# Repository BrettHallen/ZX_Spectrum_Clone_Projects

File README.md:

# ZX Spectrum Clone Projects
Hardware projects & information for Sinclair ZX Spectrum clone computers

## [Datasheets](/Datasheets)
Relevant datasheets for PCB designs.<br>

## [Astra](/Astra)
Information about the Soviet Spectrum clone.<br>

## [Belarus Byte DIN to VGA](/Belarus_Byte_DIN-to-VGA)
Convert 5-pin DIN video output to DE15 VGA:

- Pin 1 = synch
- Pin 2 = ground
- Pin 3 = blue
- Pin 4 = green
- Pin 5 = red

## [ESP32 Rainbow Nunchuck Interface](/ESP32_Rainbow_Nunchuck_Interface)
A small QWIIC-to-Nunchuck interface adaptor board for the [ESP32 Rainbow](https://www.esp32rainbow.com).

## [Leningrad-2 DIN to VGA](/Leningrad_2_DIN-to-VGA)
Convert 5-pin DIN video output to DE15 VGA:

- Pin 1 = audio
- Pin 2 = blue
- Pin 3 = red
- Pin 4 = video
- Pin 5 = green
- Sheath = ground

## [Leningrad 2 Expansion](/Leningrad_2_Expansion)
Experimental board to convert the 2x32 (2.5mm pin pitch) expansion header to standard ZX Spectrum edge connector.

## [Moldova BYTE DIN to VGA](/Moldova_BYTE_DIN-to-VGA)
There are two types of BYTE from Moldova: the "Red BYTE" (in a red case with 7-pin DIN) and the "Speccy BYTE" (looks like a Spectrum with a 5-pin DIN).

- Pin 1 = composite video (not connected)
- Pin 2 = composite synch
- Pin 3 = blue
- Pin 4 = green
- Pin 5 = red
- Pin 6 = ground
- Pin 7 = audio

## [Nafanya](/Nafanya)

## [Orel BK DIN to VGA](/Orel_BK_DIN-to-VGA)

## [RGB to VGA](/RGB_to_VGA)

## [Sirius](/Sirius)

## [ZX Spectrum Pioneer 2 Keyboard](/ZX_Spectrum_Pioneer-2_Keyboard)
Work in progress replacement.

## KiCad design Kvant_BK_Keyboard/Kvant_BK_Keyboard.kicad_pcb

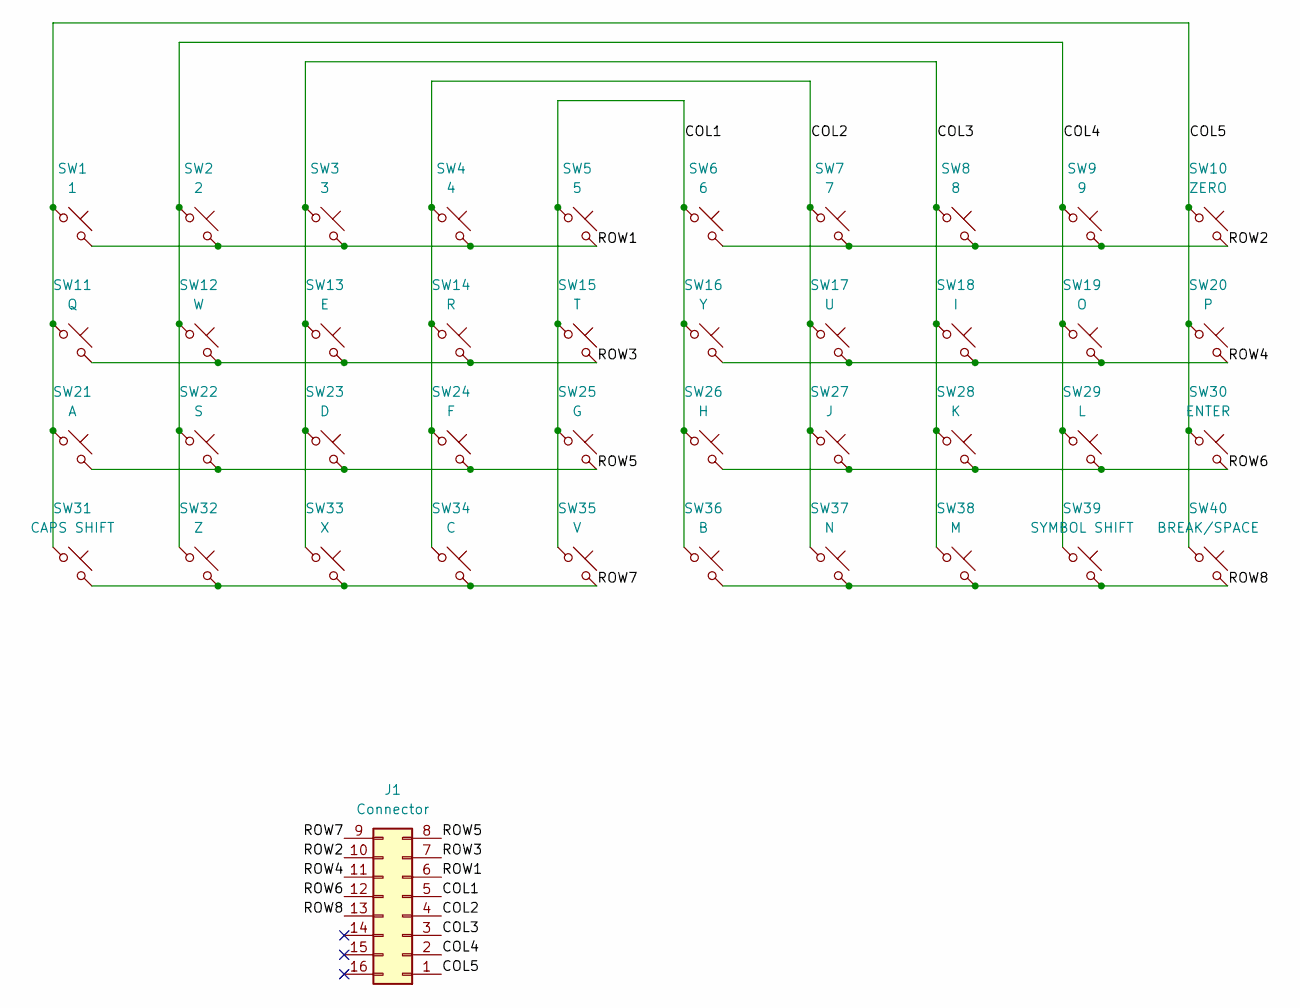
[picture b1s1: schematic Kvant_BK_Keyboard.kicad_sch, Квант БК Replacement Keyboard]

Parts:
J1: Connector; DIP-16_W7.62mm
SW1: 1; SW_KS33_1u
SW2: 2; SW_KS33_1u
SW3: 3; SW_KS33_1u
SW4: 4; SW_KS33_1u
SW5: 5; SW_KS33_1u
SW6: 6; SW_KS33_1u
SW7: 7; SW_KS33_1u
SW8: 8; SW_KS33_1u
SW9: 9; SW_KS33_1u
SW10: ZERO; SW_KS33_1u
SW11: Q; SW_KS33_1u
SW12: W; SW_KS33_1u
SW13: E; SW_KS33_1u
SW14: R; SW_KS33_1u
SW15: T; SW_KS33_1u
SW16: Y; SW_KS33_1u
SW17: U; SW_KS33_1u
SW18: I; SW_KS33_1u
SW19: O; SW_KS33_1u
SW20: P; SW_KS33_1u
SW21: A; SW_KS33_1u
SW22: S; SW_KS33_1u
SW23: D; SW_KS33_1u
SW24: F; SW_KS33_1u
SW25: G; SW_KS33_1u
SW26: H; SW_KS33_1u
SW27: J; SW_KS33_1u
SW28: K; SW_KS33_1u
SW29: L; SW_KS33_1u
SW30: ENTER; SW_KS33_1u
SW31: CAPS SHIFT; SW_KS33_1u
SW32: Z; SW_KS33_1u
SW33: X; SW_KS33_1u
SW34: C; SW_KS33_1u
SW35: V; SW_KS33_1u
SW36: B; SW_KS33_1u
SW37: N; SW_KS33_1u
SW38: M; SW_KS33_1u
SW39: SYMBOL SHIFT; SW_KS33_1u
SW40: BREAK/SPACE; SW_KS33_1u

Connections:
/COL1: J1.5, SW5.1, SW6.1, SW15.1, SW16.1, SW25.1, SW26.1, SW35.1, SW36.1
/COL2: J1.4, SW4.1, SW7.1, SW14.1, SW17.1, SW24.1, SW27.1, SW34.1, SW37.1
/COL3: J1.3, SW3.1, SW8.1, SW13.1, SW18.1, SW23.1, SW28.1, SW33.1, SW38.1
/COL4: J1.2, SW2.1, SW9.1, SW12.1, SW19.1, SW22.1, SW29.1, SW32.1, SW39.1
/COL5: J1.1, SW1.1, SW10.1, SW11.1, SW20.1, SW21.1, SW30.1, SW31.1, SW40.1
/ROW1: J1.6, SW1.2, SW2.2, SW3.2, SW4.2, SW5.2
/ROW2: J1.10, SW6.2, SW7.2, SW8.2, SW9.2, SW10.2
/ROW3: J1.7, SW11.2, SW12.2, SW13.2, SW14.2, SW15.2
/ROW4: J1.11, SW16.2, SW17.2, SW18.2, SW19.2, SW20.2
/ROW5: J1.8, SW21.2, SW22.2, SW23.2, SW24.2, SW25.2
/ROW6: J1.12, SW26.2, SW27.2, SW28.2, SW29.2, SW30.2
/ROW7: J1.9, SW31.2, SW32.2, SW33.2, SW34.2, SW35.2
/ROW8: J1.13, SW36.2, SW37.2, SW38.2, SW39.2, SW40.2

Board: 2 copper layers, 41 parts (1 on the bottom side), 13 nets, no tracks yet.

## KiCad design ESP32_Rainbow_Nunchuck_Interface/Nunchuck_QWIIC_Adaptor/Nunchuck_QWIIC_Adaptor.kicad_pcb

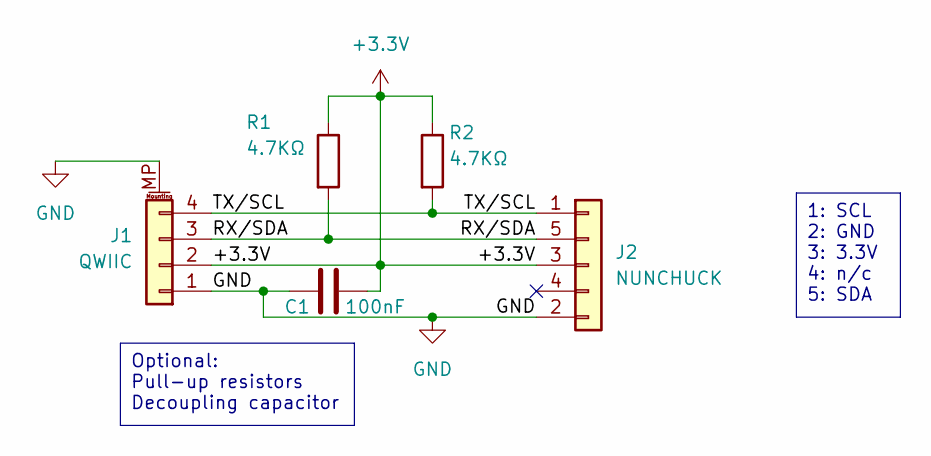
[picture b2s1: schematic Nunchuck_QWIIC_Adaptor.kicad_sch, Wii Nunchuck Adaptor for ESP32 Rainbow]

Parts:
C1: 100nF; C_0805_2012Metric_Pad1.18x1.45mm_HandSolder
J1: QWIIC; JST_SH_SM04B-SRSS-TB_1x04-1MP_P1.00mm_Horizontal
J2: NUNCHUCK; Wii_Nunchuck_Edge_Connector
R1, R2: 4.7KΩ; R_0805_2012Metric_Pad1.20x1.40mm_HandSolder

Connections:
+3.3V: C1.1, J1.2, J2.3, R1.1, R2.1
/RX/SDA: J1.3, J2.5, R1.2
/TX/SCL: J1.4, J2.1, R2.2
GND: C1.2, J1.1, J1.MP (MountPin), J2.2

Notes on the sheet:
Optional: Pull-up resistors Decoupling capacitor
1: SCL 2: GND 3: 3.3V 4: n/c 5: SDA

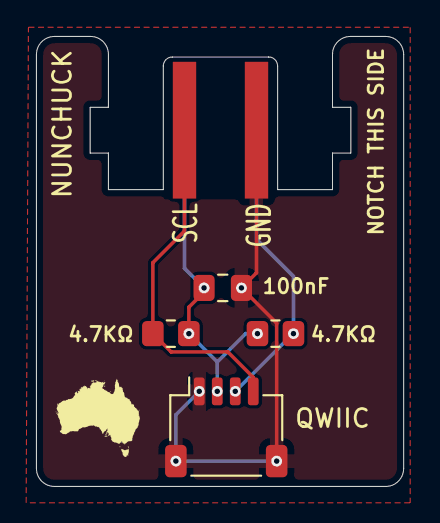
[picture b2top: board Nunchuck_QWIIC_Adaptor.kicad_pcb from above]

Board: 2 copper layers, 20.4 x 25.0 mm, 5 parts (0 on the bottom side), 4 nets.

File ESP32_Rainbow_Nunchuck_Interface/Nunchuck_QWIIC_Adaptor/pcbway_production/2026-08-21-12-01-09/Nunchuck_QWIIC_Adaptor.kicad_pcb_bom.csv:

Designator,Quantity,Value,Footprint,Package,MPN,DNP,Mount_Type,Description,KiLib_Generator
C1,1,100nF,C_0805_2012Metric_Pad1.18x1.45mm_HandSolder,,,,smt,Unpolarized capacitor,SMD_2terminal_chip_molded
J1,1,QWIIC,JST_SH_SM04B-SRSS-TB_1x04-1MP_P1.00mm_Horizontal,,,,smt,"Generic connectable mounting pin connector, single row, 01x04, script generated (kicad-library-utils/schlib/autogen/connector/)",connector/SMD_single_row_plus_mounting_pad
J2,1,NUNCHUCK,Wii_Nunchuck_Edge_Connector,,,,smt,"Generic connector, single row, 01x05, script generated (kicad-library-utils/schlib/autogen/connector/)",
"R1, R2",2,4.7KΩ,R_0805_2012Metric_Pad1.20x1.40mm_HandSolder,,,,smt,Resistor,SMD_2terminal_chip_molded

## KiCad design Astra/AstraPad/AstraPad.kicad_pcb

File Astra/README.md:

# Astra/Астра Information
A Soviet-era Sinclair ZX Spectrum clone from Minsk in the Byelorussian SSR.<br>

Its full name is "Универсальная Телеигровая Приставка Астра", or "Universal Television Game Console Astra".<br>

The files found here are from [ZXBYTE's site](https://zxbyte.org), translated to English where required and with my own additional information added.<br>

## [АСТРАПАД](/Astra/AstraPad)
My attempt at a simple Joypad-style design for the Astra.<br>

## [ROMs](/Astra/ROMs)
The Astra has two 8KB ROMs containing the modified Spectrum firmware: the changes are the [boot screen](/Astra/Images/Astra_Boot_Screen.png) and the [character font](/Astra/Images/Astra_vs_ZX_font.png) (reminds me of the Amstrad CPC font).

It also has four small PROMs - one is socketed.  I plan to (try to) dump the other three using these [Arduino sketches](/Astra/Arduino_PROM_dumper).

## [Schematics](/Astra/Schematics)
Schematics and board layout with Western-equivalent part IDs added.<br>

IMPORTANT - several of the interface pinouts have conflicting pin assignments when comparing the schematic with the manual.  The manual pinout matches my machine.<br>

## Cassette Pinout (X1)
The cassette interface uses a 5-pin DIN labelled "МАГ" (Магнетофон).<br>

IMPORTANT NOTE!  The [schematic pinout](/Astra/Schematics/X1_Pinout_RU.jpg) disagrees with the [manual pinout](/Astra/Schematics/Astra_Manual_Pinout.jpeg)!  For my machine I have used the manual's pinout.<br>

Note that the schematic lists IN FL (signal 33) and OUT FL (signal 34) but I can't see where they are used.<br>

| Pin | Signal         |
|-----|----------------|
| 1   | EAR (Вх. Маг)  |
| 2   | Ground (0V)    |
| 3   | MIC (Вых. Маг) |
| 4   | IN FL (?)      |
| 5   | OUT FL (?)     |

Now if we look at the manual's pinout:<br>

| Pin | Signal      |
|-----|-------------|
| 1   | MIC (Выход) |
| 2   | Ground (0V) |
| 3   | EAR (Вход)  |
| 4   |             |
| 5   |             |

## Video Pinout (X3)
The audio and video are output via a 2x4 РГ1Н-1 connector labelled "ТВ".  On the [schematic](/Astra/Schematics/X3_Pinout_RU.jpg) it is interface "X3".<br>

| Pin | Signal                   |
|-----|--------------------------|
| 1   | Brightness (8/16)        |
| 2   | Blue                     |
| 3   | Green                    |
| 4   | Red                      |
| 5   | Video (Видео)            |
| 6   | Audio (УНЧ)              |
| 7   | Inverted sync (Инверсия) |
| 8   | Ground (Общий)           |

The manual pinout lists pin 1 as "Полутон" or half-tone which seems to match.<br>

## Power Pinout (X4)
The power input is a 5-pin DIN labelled "БП" (Блок Питания).  On the schematic is it interface "X4", but in the [manual pinout](/Astra/Schematics/Astra_Manual_Pinout.jpeg) it is interface "X2".<br>

Note that the schematic lists ±12V but I don't see it actually used - signals 31 & 32 on the schematic - follow the manual pinout.<br>

| Pin | Signal   |
|-----|----------|
| 1   | +5V      |
| 2   |          |
| 3   | 0V       |
| 4   | -12V (?) |
| 5   | +12V (?) |

## Useful Links
- [ZXBYTE](https://zxbyte.org/astra.htm)

## Youtube Videos
- [Part 1: First look](https://youtu.be/gDP2ERXGaYo)
- [Part 2: Power on - NOK](https://youtu.be/xESQuC1y398)
- [Part 3: It works!](https://youtu.be/SmFEAmI-PiA)
- [Part 4: Loading a game](https://youtu.be/jdW-dMJSBxg)
- [Part 5: Bodging together a joypad](https://youtu.be/Pdt0EjIXJ0o)

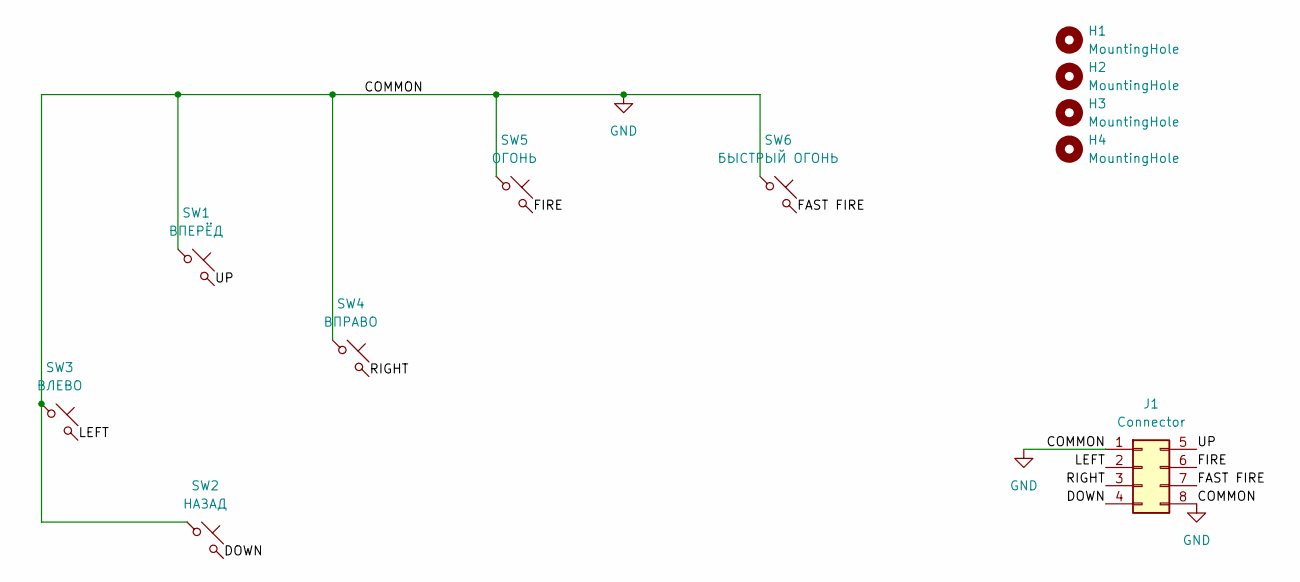
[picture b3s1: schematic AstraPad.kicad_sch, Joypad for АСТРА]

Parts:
H1, H2, H3, H4: MountingHole; MountingHole_3.2mm_M3_DIN965
J1: Connector; PinHeader_2x04_P2.54mm_Vertical
SW1: ВПЕРЁД; SW_PUSH-12mm
SW2: НАЗАД; SW_PUSH-12mm
SW3: ВЛЕВО; SW_PUSH-12mm
SW4: ВПРАВО; SW_PUSH-12mm
SW5: ОГОНЬ; SW_PUSH-12mm
SW6: БЫСТРЫЙ ОГОНЬ; SW_PUSH-12mm

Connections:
/DOWN: J1.4, SW2.2
/FAST FIRE: J1.7, SW6.2
/FIRE: J1.6, SW5.2
/LEFT: J1.2, SW3.2
/RIGHT: J1.3, SW4.2
/UP: J1.5, SW1.2
GND: J1.1, J1.8, SW1.1, SW2.1, SW3.1, SW4.1, SW5.1, SW6.1

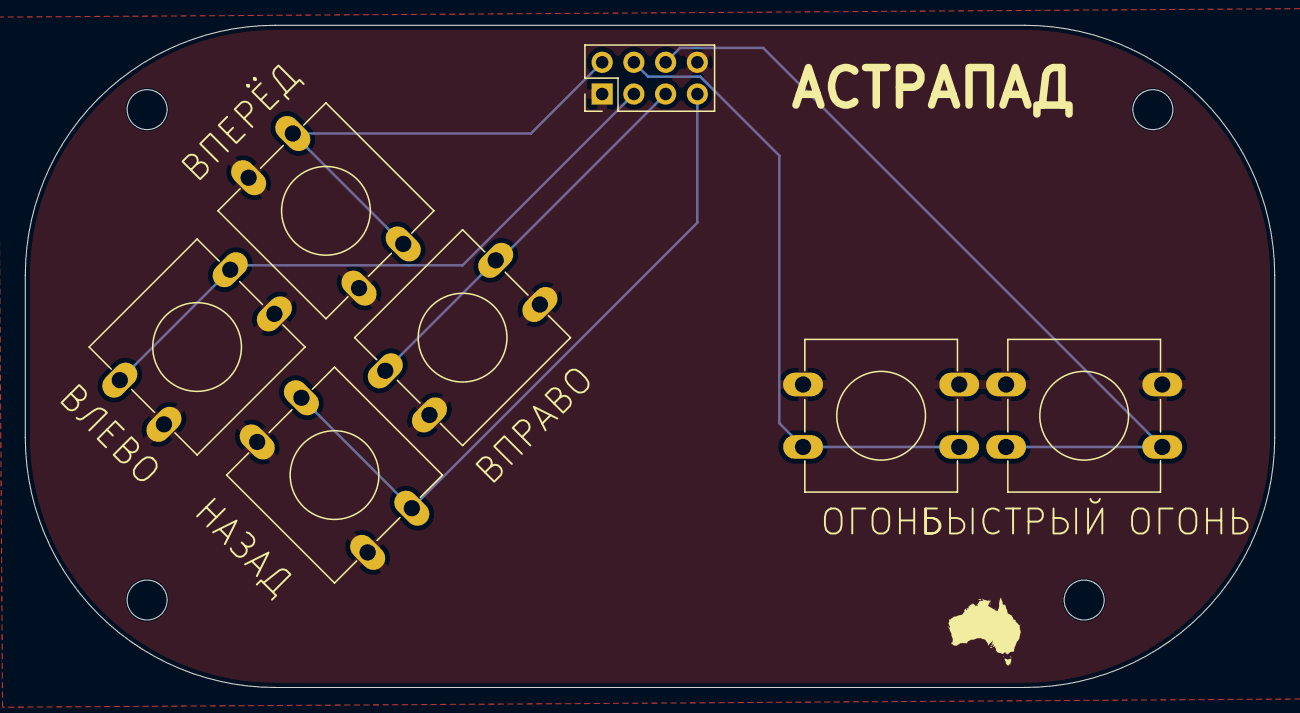
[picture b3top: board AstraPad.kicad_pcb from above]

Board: 2 copper layers, 100.0 x 53.0 mm, 11 parts (0 on the bottom side), 7 nets.

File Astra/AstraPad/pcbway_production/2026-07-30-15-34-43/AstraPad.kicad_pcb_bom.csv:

Designator,Quantity,Value,Footprint,Package,MPN,DNP,Mount_Type,Description,KiLib_Generator
J1,1,Connector,PinHeader_2x04_P2.54mm_Vertical,,,,tht,"Generic connector, double row, 02x04, top/bottom pin numbering scheme (row 1: 1...pins_per_row, row2: pins_per_row+1 ... num_pins), script generated (kicad-library-utils/schlib/autogen/connector/)",connector/pin_header_socket
SW1,1,ВПЕРЁД,SW_PUSH-12mm,,,,tht,"Push button switch, normally open, two pins, 45° tilted",
SW2,1,НАЗАД,SW_PUSH-12mm,,,,tht,"Push button switch, normally open, two pins, 45° tilted",
SW3,1,ВЛЕВО,SW_PUSH-12mm,,,,tht,"Push button switch, normally open, two pins, 45° tilted",
SW4,1,ВПРАВО,SW_PUSH-12mm,,,,tht,"Push button switch, normally open, two pins, 45° tilted",
SW5,1,ОГОНЬ,SW_PUSH-12mm,,,,tht,"Push button switch, normally open, two pins, 45° tilted",
SW6,1,БЫСТРЫЙ ОГОНЬ,SW_PUSH-12mm,,,,tht,"Push button switch, normally open, two pins, 45° tilted",

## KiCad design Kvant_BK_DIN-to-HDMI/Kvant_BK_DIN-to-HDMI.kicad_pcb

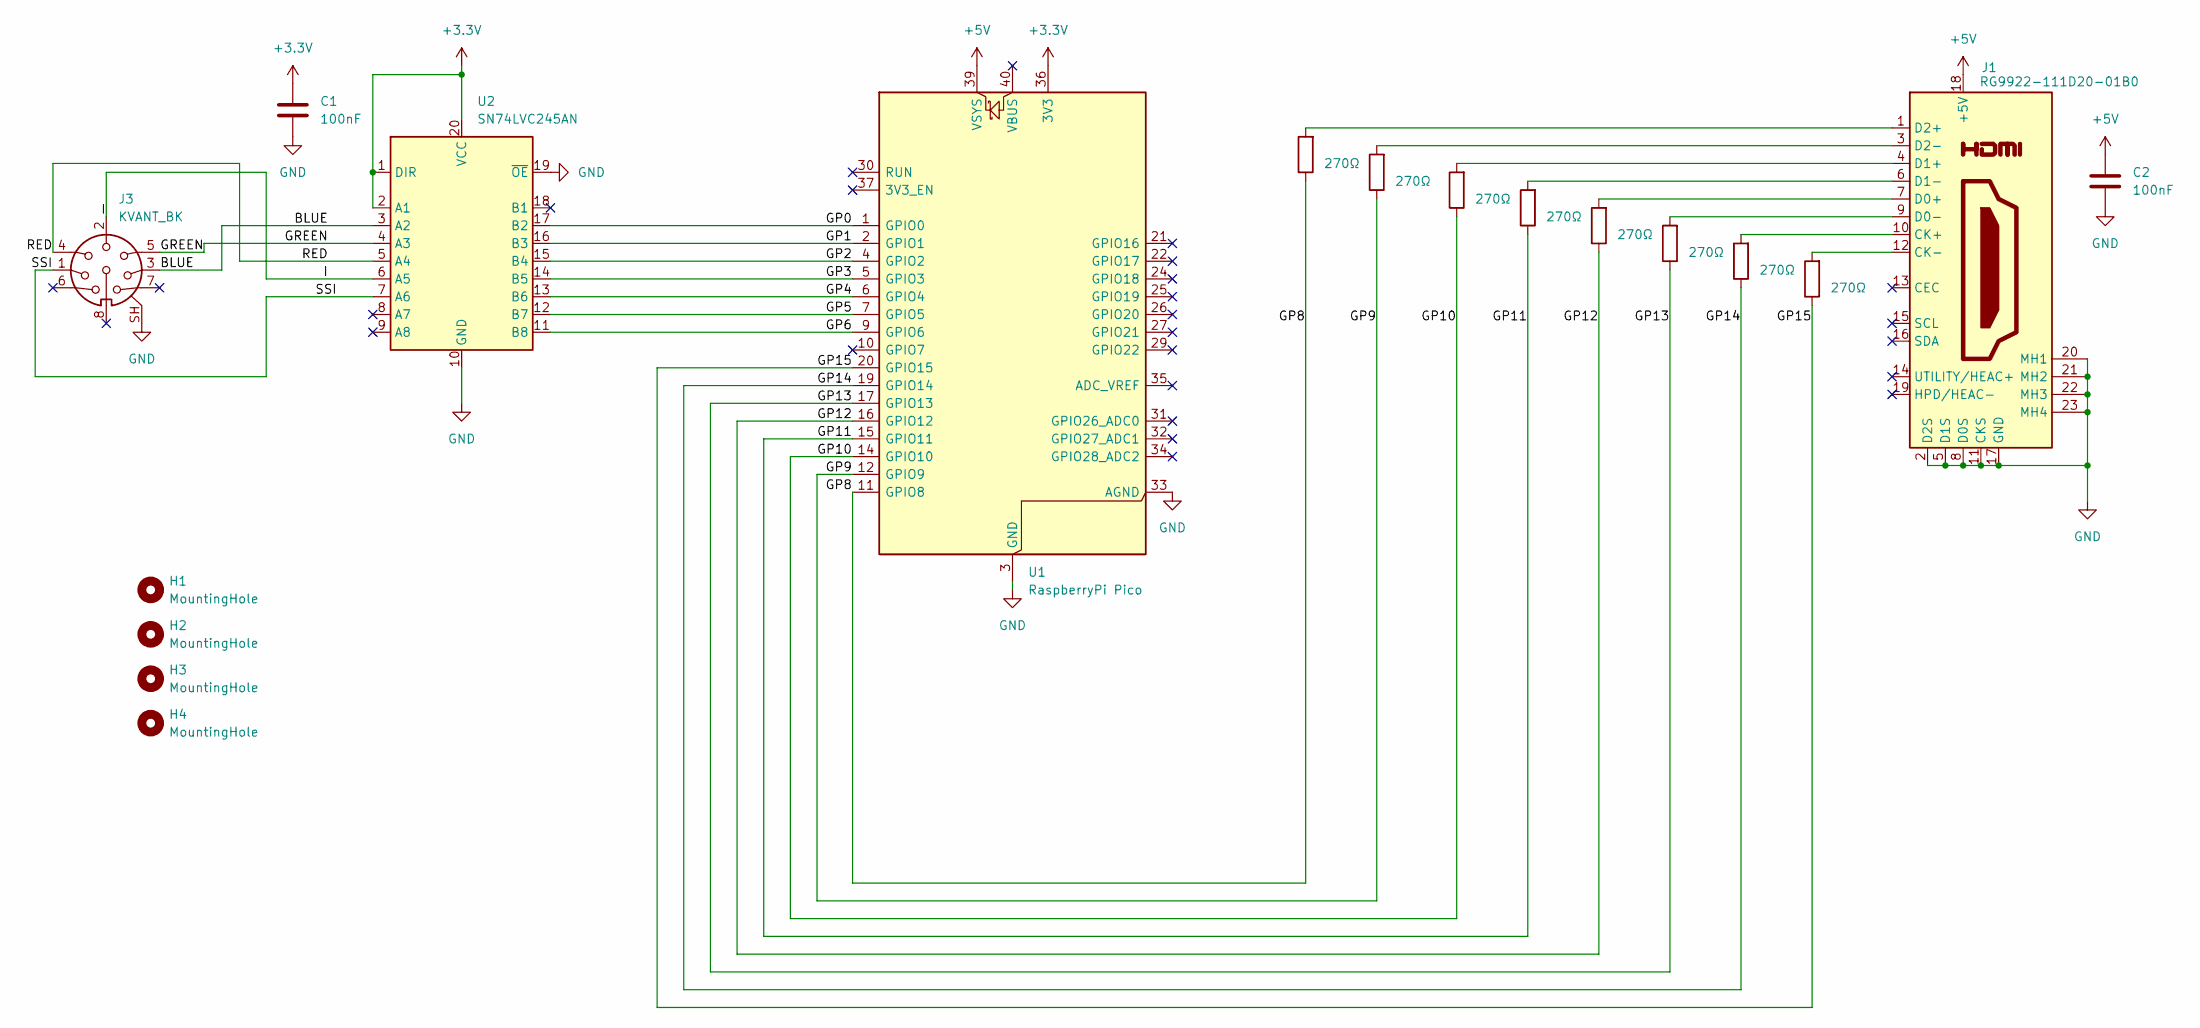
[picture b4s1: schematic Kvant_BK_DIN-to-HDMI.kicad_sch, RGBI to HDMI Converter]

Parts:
C1, C2: 100nF; C_Disc_D3.8mm_W2.6mm_P2.50mm
H1, H2, H3, H4: MountingHole; MountingHole_3.2mm_M3
J1: RG9922-111D20-01B0; RG9922111D2001B0; Manufacturer_Part_Number RG9922-111D20-01B0
J3: KVANT_BK; SDF80J
R1, R2, R3, R4, R5, R6, R7, R8: 270Ω; R_Axial_DIN0207_L6.3mm_D2.5mm_P7.62mm_Horizontal
U1: RaspberryPi Pico; RaspberryPi_Pico_Common_Unspecified
U2: SN74LVC245AN; DIP-20_W7.62mm

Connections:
+3.3V: C1.1, U1.36 (3V3), U2.1 (DIR), U2.2 (A1), U2.20 (VCC)
+5V: C2.1, J1.18 (+5V), U1.39 (VSYS); also elsewhere on the board
/B: J3.3, U2.3 (A2); also elsewhere on the board
/F: U2.9 (A8); also elsewhere on the board
/G: J3.5, U2.4 (A3); also elsewhere on the board
/GP0: U1.1 (GPIO0), U2.17 (B2)
/GP1: U1.2 (GPIO1), U2.16 (B3)
/GP2: U1.4 (GPIO2), U2.15 (B4)
/GP3: U1.5 (GPIO3), U2.14 (B5)
/GP4: U1.6 (GPIO4), U2.13 (B6)
/GP5: U1.7 (GPIO5), U2.12 (B7)
/GP6: U1.9 (GPIO6), U2.11 (B8)
/GP8: R8.1, U1.11 (GPIO8)
/GP9: R7.1, U1.12 (GPIO9)
/GP10: R6.1, U1.14 (GPIO10)
/GP11: R5.1, U1.15 (GPIO11)
/GP12: R4.1, U1.16 (GPIO12)
/GP13: R3.1, U1.17 (GPIO13)
/GP14: R2.1, U1.19 (GPIO14)
/GP15: R1.1, U1.20 (GPIO15)
/I: J3.2, U2.6 (A5); also elsewhere on the board
/KSI: U2.8 (A7); also elsewhere on the board
/R: J3.4, U2.5 (A4); also elsewhere on the board
/SSI: J3.1, U2.7 (A6); also elsewhere on the board
GND: C1.2, C2.2, J1.2 (D2S), J1.5 (D1S), J1.8 (D0S), J1.11 (CKS), J1.17 (GND), J1.20 (MH1), J1.21 (MH2), J1.22 (MH3), J1.23 (MH4), J3.SH, U1.3 (GND), U1.8 (GND), U1.13 (GND), U1.18 (GND), U1.23 (GND), U1.28 (GND), U1.33 (AGND), U1.38 (GND), U2.10 (GND), U2.19 (~OE); also elsewhere on the board
unnamed: J1.10 (CK+), R2.2
unnamed: J1.12 (CK-), R1.2
unnamed: J1.7 (D0+), R4.2
unnamed: J1.9 (D0-), R3.2
unnamed: J1.4 (D1+), R6.2
unnamed: J1.6 (D1-), R5.2
unnamed: J1.1 (D2+), R8.2
unnamed: J1.3 (D2-), R7.2

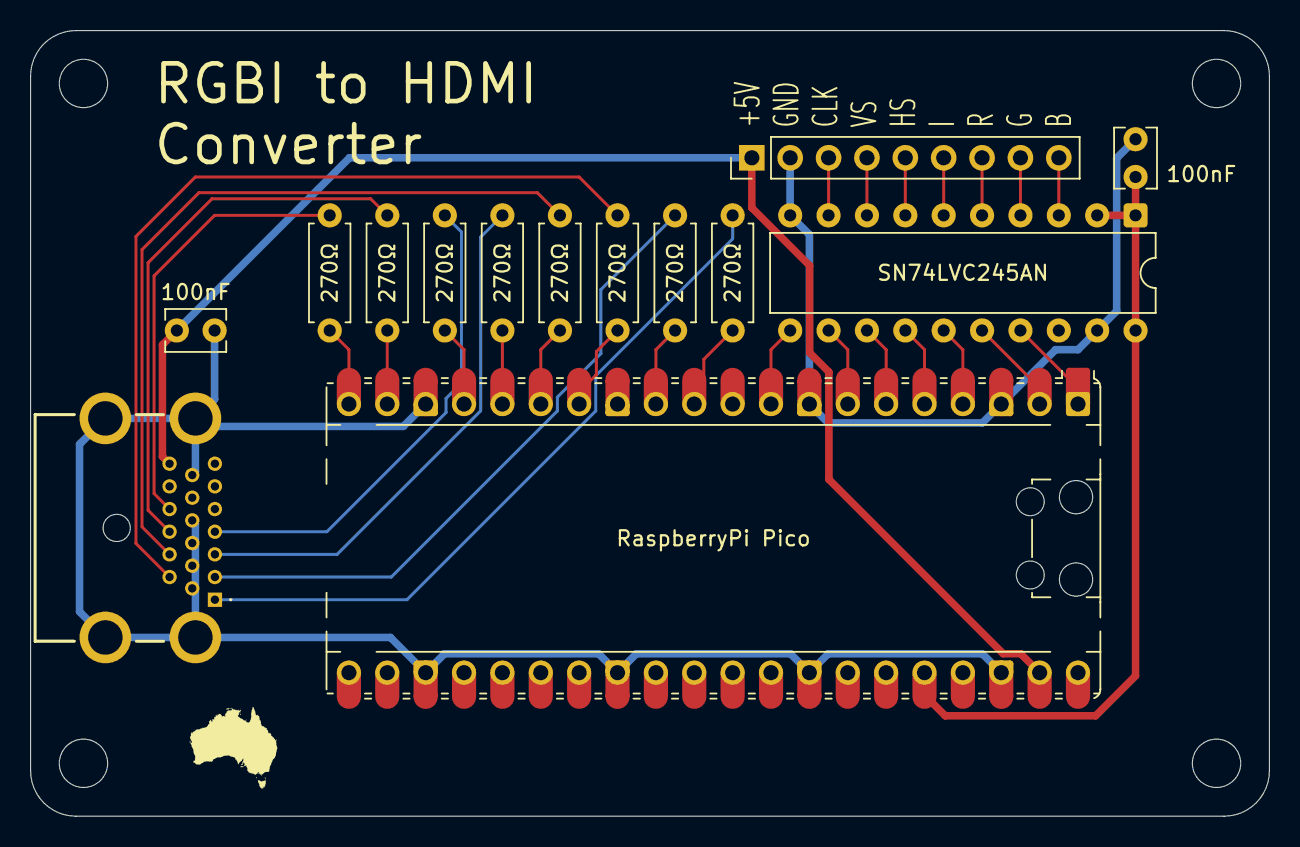
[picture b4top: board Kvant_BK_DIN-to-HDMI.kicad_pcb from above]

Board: 2 copper layers, 82.0 x 52.0 mm, 18 parts (0 on the bottom side), 33 nets.

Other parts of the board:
J2: From Computer; PinHeader_1x09_P2.54mm_Vertical

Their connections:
+5V: J2.1; also elsewhere on the board
/B: J2.9; also elsewhere on the board
/F: J2.3; also elsewhere on the board
/G: J2.8; also elsewhere on the board
/I: J2.6; also elsewhere on the board
/KSI: J2.4; also elsewhere on the board
/R: J2.7; also elsewhere on the board
/SSI: J2.5; also elsewhere on the board
GND: J2.2; also elsewhere on the board

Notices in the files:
parts and their libraries:
Geometry derived from the open-source Adafruit Wii Nunchuck Breakout Adapter (PID 4836, CC-BY-SA).
